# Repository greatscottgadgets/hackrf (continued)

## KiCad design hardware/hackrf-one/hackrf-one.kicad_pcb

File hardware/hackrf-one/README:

HackRF One is a wideband software radio transceiver with a USB interface.

hardware notes:

Schematic and layout files were designed in KiCad, an open source electronic
design automation package.

order of copper layers:
    Copper 1:  C1F (front)
    Copper 2:  C2
    Copper 3:  C3
    Copper 4:  C4B (back)

PCB description: 4 layer PCB 1.6 mm
    Copper    1   0.035 mm
    Prepreg 1-2   0.2104 mm
    Copper    2   0.0152 mm
    Core    2-3   1.065 mm
    Copper    3   0.0152 mm
    Prepreg 3-4   0.2104 mm
    Copper    4   0.035 mm

7628 prepreg with Er=4.6 (+/- 0.1)
required impedance: 50 ohm (+/- 5%) 11.55 mil microstrip impedance
double side solder mask green
single side silkscreen white
5 mil min trace width and
5 mil min isolation

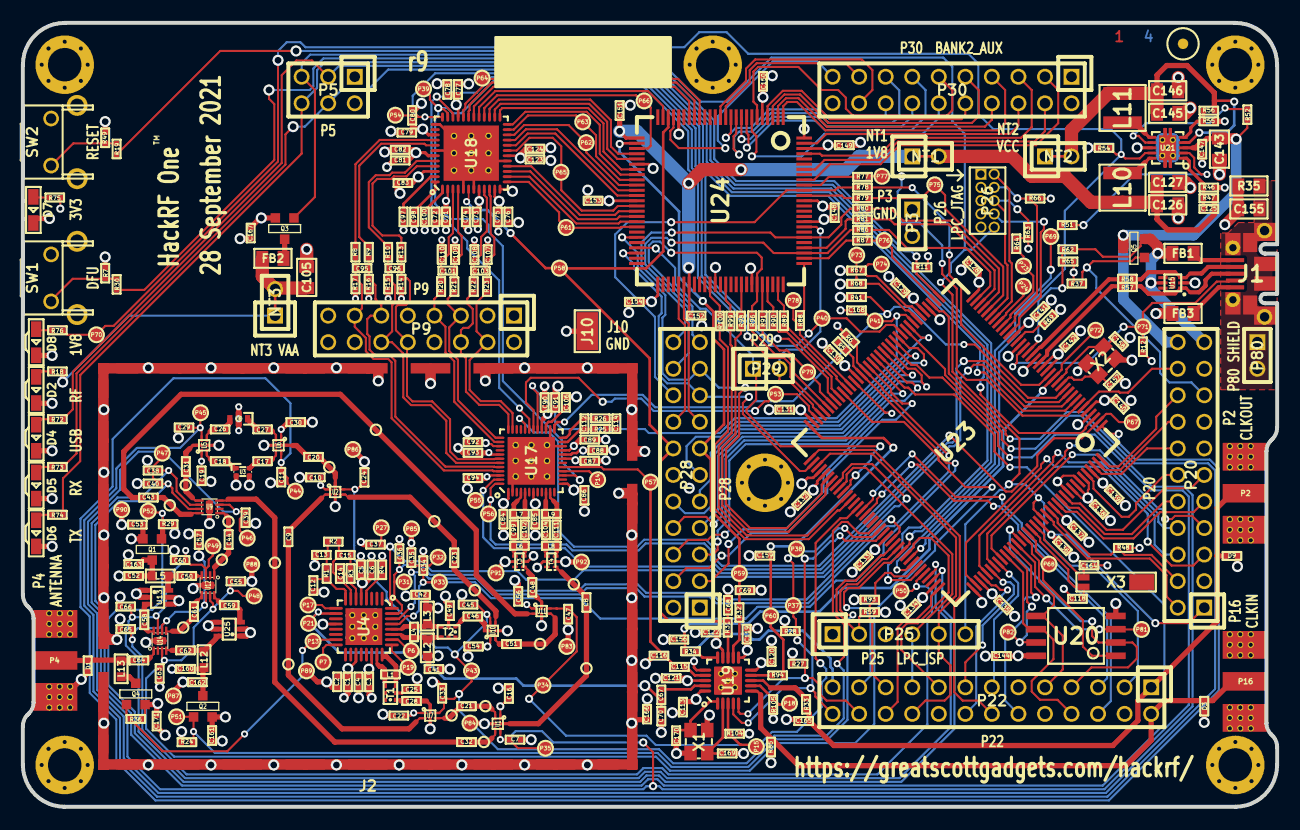
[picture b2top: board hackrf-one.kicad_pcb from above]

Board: 4 copper layers, 120.0 x 75.0 mm, 431 parts (0 on the bottom side), 315 nets.

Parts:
C1, C3, C5, C7, C11, C24, C29, C33, C34, C35, C36, C37, C38, C39, C40, C45, C47, C55, C57, C60, C63, C65, C66, C67, C115, C125: 33pF; GSG-0402
C2, C4, C6, C10, C16, C19, C22, C30, C54, C56, C87, C88, C89, C92, C93, C162, C163: 10nF; GSG-0402
C8, C21, C32, C43, C48, C51, C84, C85, C86, C94, C95, C96, C99, C101, C102, C103, C107, C108, C109, C110: 22pF; GSG-0402
C9, C17, C18, C20, C23, C25, C28, C31, C44, C46, C49, C50, C58, C59, C61, C62, C64, C71, C73, C75, C77, C79, C81, C83, C91, C113, C119, C120, C121, C122, C123, C128, C129, C130, C131, C132, C133, C134, C135, C136, C137, C138, C139, C140, C141, C142, C144, C147, C148, C149, C150, C151, C152, C153, C154, C166, C167: 100nF; GSG-0402
C12, C13: 330pF; GSG-0402
C14: 8p2; GSG-0402
C15, C112: 180pF; GSG-0402
C26, C27, C116, C156: 47pF; GSG-0402
C41, C42, C52, C68, C69, C70, C90, C159, C160, C165, C168: 100pF; GSG-0402
C53, C106, C161, C171: 1uF; GSG-0402
C72, C74, C76, C78, C80, C82, C124: 2.2uF; GSG-0402
C97, C98, C100: 330nF; GSG-0402
C104, C111: 3pF; GSG-0402
C105, C126, C127, C143, C145, C146: 10uF; GSG-0805
C114: 3.3nF; GSG-0402
C118, C157, C158, C164: 18pF; GSG-0402
C155: DNP; GSG-0805
C169, C170: 1.8pF; GSG-0402
D1, D3, D9: GSG-DIODE-TVS-BI; GSG-0402
D2: VAALED; LTST-S220
D4: USBLED; LTST-S220
D5: RXLED; LTST-S220
D6: TXLED; LTST-S220
D7: VCCLED; LTST-S220
D8: 1V8LED; LTST-S220
FB1, FB2, FB3: FILTER; GSG-0805
J1: USB-MICRO-B; GSG-USB-MICROB-FCI-10103592-EXT
J2: RF-SHIELD-FRAME; GSG-SHIELD-BMI-S-230
J3: RF-SHIELD-COVER; GSG-NULL-MODULE
J4, J5, J6, J7, J8, J9: MOUNTING_HOLE; GSG-HOLE126MIL-COPPER
J10: GND_CLIP; GSG-TEST-POINT-S1751-46R
L1, L4, L6, L8, L9: DNP; GSG-0402
L2, L3, L5, L12, L13: 10uH; GSG-0603
L7: 6.2nH; GSG-0402
L10, L11: 4u7; GSG-NRG4026
MARK1MM: VAL**; GSG-MARK1MM
NT1: 1V8; HEADER-1x2-SHORTED
NT2: VCC; HEADER-1x2-SHORTED
NT3: VAA; HEADER-1x2-SHORTED
P2: CLKOUT; GSG-SMA-73251-2120
P3: GND; GSG-HEADER-NOMARK-1x2
P4: ANTENNA; GSG-SMA-73251-2120
P5: LEDS; GSG-HEADER-2x3
P6: GPO4; GSG-TESTPOINT-50MIL
P7: GPO2; GSG-TESTPOINT-50MIL
P9: BASEBAND; GSG-HEADER-2x8
P13: GPO1; GSG-TESTPOINT-50MIL
P14: XCVR_CLKOUT; GSG-TESTPOINT-50MIL
P15: INTR; GSG-TESTPOINT-50MIL
P16: CLKIN; GSG-SMA-73251-2120
P17: GPO6; GSG-TESTPOINT-50MIL
P18: OEB; GSG-TESTPOINT-50MIL
P19: GPO3; GSG-TESTPOINT-50MIL
P20: GPIO; GSG-HEADER-2x11
P21: REF_IN; GSG-TESTPOINT-50MIL
P22: I2S; GSG-HEADER-2x13
P23: DBGEN; GSG-TESTPOINT-50MIL
P24: TRST; GSG-TESTPOINT-50MIL
P25: LPC_ISP; GSG-HEADER-1x6
P26: LPC_JTAG; GSG-50MIL-HEADER-2x5-TH
P27: MIXER_SDATA; GSG-TESTPOINT-50MIL
P28: SD; GSG-HEADER-2x11
P29: CPLD_JTAG; GSG-HEADER-1x2
P30: BANK2_AUX; GSG-HEADER-2x10
P31: MIXER_SCLK; GSG-TESTPOINT-50MIL
P32: MIXER_ENX; GSG-TESTPOINT-50MIL
P33: MIXER_RESETX; GSG-TESTPOINT-50MIL
P34: MIX_BYPASS; GSG-TESTPOINT-50MIL
P35: !MIX_BYPASS; GSG-TESTPOINT-50MIL
P37: SCL; GSG-TESTPOINT-50MIL
P38: SDA; GSG-TESTPOINT-50MIL
P39: SSP1_SCK; GSG-TESTPOINT-50MIL
P40: SSP1_COPI; GSG-TESTPOINT-50MIL
P41: SSP1_CIPO; GSG-TESTPOINT-50MIL
P43: RX; GSG-TESTPOINT-50MIL
P44: HP; GSG-TESTPOINT-50MIL
P45: LP; GSG-TESTPOINT-50MIL
P46: TX_MIX_BP; GSG-TESTPOINT-50MIL
P47: RX_MIX_BP; GSG-TESTPOINT-50MIL
P48: TX_AMP; GSG-TESTPOINT-50MIL
P49: RX_AMP; GSG-TESTPOINT-50MIL
P50: AMP_BYPASS; GSG-TESTPOINT-50MIL
P51: !TX_AMP_PWR; GSG-TESTPOINT-50MIL
P52: !RX_AMP_PWR; GSG-TESTPOINT-50MIL
P53: CS_XCVR; GSG-TESTPOINT-50MIL
P54: CS_AD; GSG-TESTPOINT-50MIL
P55: TXENABLE; GSG-TESTPOINT-50MIL
P56: RXENABLE; GSG-TESTPOINT-50MIL
P57: XTAL2; GSG-TESTPOINT-50MIL
P58: GCK1; GSG-TESTPOINT-50MIL
P59: GCK2; GSG-TESTPOINT-50MIL
P60: SGPIO_CLK; GSG-TESTPOINT-50MIL
P61: DA0; GSG-TESTPOINT-50MIL
P62: DA7; GSG-TESTPOINT-50MIL
P63: DD0; GSG-TESTPOINT-50MIL
P64: DD9; GSG-TESTPOINT-50MIL
P65: DA4; GSG-TESTPOINT-50MIL
P66: DD5; GSG-TESTPOINT-50MIL
P67: RSSI; GSG-TESTPOINT-50MIL
P68: SPIFI_CS; GSG-TESTPOINT-50MIL
P69: VREGMODE; GSG-TESTPOINT-50MIL
P70: EN_1V8; GSG-TESTPOINT-50MIL
P71: ID; GSG-TESTPOINT-50MIL
P72, P75, P76, P77, P78, P79: GP_CLKIN; GSG-TESTPOINT-50MIL
P73: P1_2; GSG-TESTPOINT-50MIL
P74: P1_1; GSG-TESTPOINT-50MIL
P80: SHIELD; GSG-HEADER-NOMARK-1x2
P81: SPIFI_SIO2; GSG-TESTPOINT-50MIL
P82: SPIFI_SIO3; GSG-TESTPOINT-50MIL
P83, P84, P85, P86, P87, P88, P89, P90, P91, P92: GND; GSG-TESTPOINT-50MIL
Q1, Q2, Q3, Q4, Q5: MOSFET_P; SOT23-3
R1, R2, R72, R75: 470; GSG-0402
R3: 22k; GSG-0402
R4: 51k; GSG-0402
R5, R6, R7, R11, R12, R24, R29, R36, R37, R41, R48, R49, R51, R52, R54, R59, R62, R63, R64, R66, R67, R68, R85, R93, R104, R105: 10k; GSG-0402
R8, R9, R10, R13, R73, R76: 1k; GSG-0402
R14, R15, R16, R17: 4k7; GSG-0402
R18, R27, R28, R74: 1k8; GSG-0402
R19, R30, R31, R32, R33, R34, R77, R78, R79, R80, R81, R86, R87, R88, R89, R90, R91, R94, R96, R98, R99, R100: 39; GSG-0402
R20, R21, R22, R23, R57, R58: 0; GSG-0402
R25, R26: 475; GSG-0402
R35: DNP; GSG-0805
R46, R55: 162k; GSG-0402
R47: 330k; GSG-0402
R56: 715k; GSG-0402
R65: 18k; GSG-0402
R69: 12k; GSG-0402
SW1: DFU; GSG-SWITCH-FSMRA
SW2: RESET; GSG-SWITCH-FSMRA
T1: MIX_IN_BALUN; GSG-B0310J50100AHF
T2: MIX_OUT_BALUN; GSG-B0310J50100AHF
T3: RX_BALUN; GSG-2500BL14M100
T4: TX_BALUN; GSG-2500BL14M100
TESTPOINT-30MIL-MASKONLY, TESTPOINT-30MIL-MASKONLY#2, TESTPOINT-30MIL-MASKONLY#3, TESTPOINT-30MIL-MASKONLY#4, TESTPOINT-30MIL-MASKONLY#5, TESTPOINT-30MIL-MASKONLY#6, TESTPOINT-30MIL-MASKONLY#7, TESTPOINT-30MIL-MASKONLY#8, TESTPOINT-30MIL-MASKONLY#9, TESTPOINT-30MIL-MASKONLY#10, TESTPOINT-30MIL-MASKONLY#11, TESTPOINT-30MIL-MASKONLY#12, TESTPOINT-30MIL-MASKONLY#13, TESTPOINT-30MIL-MASKONLY#14, TESTPOINT-30MIL-MASKONLY#15, TESTPOINT-30MIL-MASKONLY#16, TESTPOINT-30MIL-MASKONLY#17: VAL**; GSG-TESTPOINT-30MIL-MASKONLY
U1, U2, U5, U6, U7, U10, U11: SKY13453; SKY13350-385LF
U3: RX_LOWPASS_FILTER; GSG-LP0603
U4: RFFC5072; GSG-QFN32
U8: RX_HIGHPASS_FILTER; GSG-HP-DEA
U9, U12, U14: SKY13317; GSG-SKY13317-373LF
U13, U25: MGA-81563; GSG-SOT363
U15: TVS; GSG-LXES1TBCC2-004
U17: MAX2837; GSG-QFN48-6
U18: MAX5864; GSG-QFN48-7
U19: SI5351C; GSG-QFN20-4
U20: W25Q80; GSG-SOIC8-208
U21: TPS62410; GSG-S-PVSON-N10
U23: LPC4320FBD144; GSG-LQFP144
U24: GSG-XC2C64A-7VQG100C; GSG-VQ100
X1: GSG-XTAL4PIN; GSG-XTAL3.2x2.5mm
X2: MCU_XTAL; GSG-XTAL3.2x2.5mm
X3: RTC_XTAL; GSG-XTAL-AB26TRQ

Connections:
!MIX_BYPASS: C7.2, C38.2, P35.1, U1.5, U9.6, U23.50
!RX_AMP_PWR: P52.1, Q1.1, R29.2, U23.106
!TX_AMP_PWR: P51.1, Q2.1, R24.1, U23.97
!VAA_ENABLE: P5.5, Q3.1, R11.2, U23.37
+1V8: C151.1, C152.1, NT1.1, U24.26, U24.57
/baseband/CLK0: R31.2, U19.13
/baseband/CLK1: R32.2, U19.12
/baseband/CLK2: R94.2, U19.9
/baseband/CLK3: R33.2, U19.8
/baseband/CLK5: C115.1, U19.17
/baseband/COM: C97.1, U18.47
/baseband/CPOUT+: C112.2, R25.1, U17.23
/baseband/CPOUT-: C112.1, R26.1, U17.24
/baseband/IA+: C101.1, C110.1, R20.1, U18.3
/baseband/IA-: C101.2, C109.1, R21.1, U18.4
/baseband/ID+: R13.1, U18.45
/baseband/ID-: R10.1, U18.44
/baseband/INTR: P15.1, R104.2, U19.3
/baseband/OEB: P18.1, R105.2, U19.7
/baseband/QA+: C103.2, C107.1, R23.1, U18.10
/baseband/QA-: C103.1, C108.1, R22.1, U18.9
/baseband/QD+: R8.1, U18.40
/baseband/QD-: R9.1, U18.41
/baseband/REFN: C98.1, U18.48
/baseband/REFP: C100.1, U18.1
/baseband/RXBBI+: P9.7, R20.2, U17.38
/baseband/RXBBI-: P9.5, R21.2, U17.37
/baseband/RXBBQ+: P9.6, R22.2, U17.36
/baseband/RXBBQ-: P9.4, R23.2, U17.35
/baseband/TXBBI+: C96.1, P9.12, R10.2, R15.1, U17.43
/baseband/TXBBI-: C96.2, P9.10, R13.2, R14.1, U17.42
/baseband/TXBBQ+: C95.2, P9.11, R9.2, R16.1, U17.44
/baseband/TXBBQ-: C95.1, P9.13, R8.2, R17.1, U17.45
/baseband/XA: C170.2, U19.1, X1.3
/baseband/XB: C169.2, U19.2, X1.1
/baseband/XCVR_CLKOUT: P14.1, U17.16
/baseband/XTAL2: C115.2, C116.1, P57.1, U17.17
/frontend/!ANT_BIAS: P13.1, Q4.1, R36.1, U4.15
/frontend/REF_IN: C67.2, C70.1, P21.1, U4.10
/frontend/RX_AMP_IN: C58.1, U14.8
/frontend/RX_AMP_OUT: C50.2, U12.4
/frontend/TX_AMP_IN: C59.1, U12.8
/frontend/TX_AMP_OUT: C62.1, U14.4
/mcu/usb/power/ADC0_0: P20.20, U23.6
/mcu/usb/power/ADC0_2: P20.16, U23.143
/mcu/usb/power/ADC0_5: P20.18, U23.144
/mcu/usb/power/ADC0_6: P20.14, U23.142
/mcu/usb/power/B1AUX13: P28.16, U24.55
/mcu/usb/power/B1AUX14: P28.15, U24.56
/mcu/usb/power/B2AUX1: P30.18, U24.13
/mcu/usb/power/B2AUX2: P30.17, U24.12
/mcu/usb/power/B2AUX3: P30.16, U24.11
/mcu/usb/power/B2AUX4: P30.15, U24.10
/mcu/usb/power/B2AUX5: P30.14, U24.9
/mcu/usb/power/B2AUX6: P30.13, U24.8
/mcu/usb/power/B2AUX7: P30.12, U24.7
/mcu/usb/power/B2AUX8: P30.11, U24.6
/mcu/usb/power/B2AUX9: P30.10, U24.4
/mcu/usb/power/B2AUX10: P30.9, U24.3
/mcu/usb/power/B2AUX11: P30.8, U24.2
/mcu/usb/power/B2AUX12: P30.7, U24.1
/mcu/usb/power/B2AUX13: P30.6, U24.99
/mcu/usb/power/B2AUX14: P30.5, U24.97
/mcu/usb/power/B2AUX15: P30.4, U24.94
/mcu/usb/power/B2AUX16: P30.3, U24.92
/mcu/usb/power/BANK2F3M1: R77.2, U24.91
/mcu/usb/power/BANK2F3M2: P28.18, R78.2, U24.90
/mcu/usb/power/BANK2F3M3: R79.2, U24.89
/mcu/usb/power/BANK2F3M4: P28.22, R80.2, U24.81
/mcu/usb/power/BANK2F3M5: R81.2, U24.79
/mcu/usb/power/BANK2F3M6: P28.20, R86.2, U24.78
/mcu/usb/power/BANK2F3M7: R87.2, U24.77
/mcu/usb/power/BANK2F3M8: R88.2, U24.76
/mcu/usb/power/BANK2F3M9: R89.2, U24.74
/mcu/usb/power/BANK2F3M10: R90.2, U24.72
/mcu/usb/power/BANK2F3M11: R91.2, U24.71
/mcu/usb/power/BANK2F3M12: P28.21, R96.2, U24.70
/mcu/usb/power/BANK2F3M14: R98.2, U24.67
/mcu/usb/power/BANK2F3M15: R99.2, U24.64
/mcu/usb/power/BANK2F3M16: R100.2, U24.61
/mcu/usb/power/CPLD_TCK: P28.17, U23.74, U24.48
/mcu/usb/power/CPLD_TDI: P28.19, U23.78, U24.45
/mcu/usb/power/CPLD_TDO: P29.2, U23.69, U24.83
/mcu/usb/power/CPLD_TMS: P29.1, U23.82, U24.47
/mcu/usb/power/DBGEN: P23.1, R64.1, U23.28
/mcu/usb/power/DM: R58.1, U23.20
/mcu/usb/power/DP: R57.1, U23.18
/mcu/usb/power/EN1V8: P70.1, R54.2, R76.2, U21.9, U23.100
/mcu/usb/power/GCK0: P30.19, U24.22
/mcu/usb/power/GPIO3_8: P20.5, U23.110
/mcu/usb/power/GPIO3_9: P20.6, U23.113
/mcu/usb/power/GPIO3_10: P20.7, U23.115
/mcu/usb/power/GPIO3_11: P20.8, U23.117
/mcu/usb/power/GPIO3_12: P20.9, U23.132
/mcu/usb/power/GPIO3_13: P20.10, U23.133
/mcu/usb/power/GPIO3_14: P20.11, U23.134
/mcu/usb/power/GPIO3_15: P20.12, U23.140
/mcu/usb/power/GP_CLKIN: C156.1, P72.1, R34.1, U23.14
/mcu/usb/power/I2C1_SCL: P22.5, U23.88
/mcu/usb/power/I2C1_SDA: P22.6, U23.87
/mcu/usb/power/I2S0_RX_MCLK: P22.14, U23.73
/mcu/usb/power/I2S0_RX_SCK: P22.12, U23.120
/mcu/usb/power/I2S0_RX_SDA: P22.13, U23.116
/mcu/usb/power/I2S0_RX_WS: P22.15, U23.114
/mcu/usb/power/I2S0_TX_MCLK: P22.17, U23.99
/mcu/usb/power/I2S0_TX_SCK: P22.16, U23.112
/mcu/usb/power/ISP: P25.2, R59.2, U23.96
/mcu/usb/power/LED1: P5.3, R72.2, U23.3
/mcu/usb/power/LED2: P5.4, R73.2, U23.8
/mcu/usb/power/LED3: P5.6, R74.2, U23.103
/mcu/usb/power/P1_1: P74.1, R67.1, U23.42
/mcu/usb/power/P1_2: P73.1, R68.1, U23.43
/mcu/usb/power/P2_8: P22.23, R30.1, U23.98
/mcu/usb/power/P2_9: P22.21, R93.1, U23.102
/mcu/usb/power/P2_13: P22.22, U23.108
/mcu/usb/power/REG_OUT1: C145.2, C146.2, L11.1, NT2.2, R56.1, U21.4
/mcu/usb/power/REG_OUT2: C125.1, C126.1, C127.1, L10.2, NT1.2, R47.1
/mcu/usb/power/RESET: P22.3, P25.6, P26.10, R19.1, U23.128
/mcu/usb/power/RREF: R69.1, U23.24
/mcu/usb/power/RTCX1: C118.1, U23.125, X3.2
/mcu/usb/power/RTCX2: C164.1, U23.126, X3.1
/mcu/usb/power/RTC_ALARM: P20.2, U23.129
/mcu/usb/power/SD_CD: P28.3, U23.60
/mcu/usb/power/SD_CLK: P28.11, U23.45
/mcu/usb/power/SD_CMD: P28.9, U23.49
/mcu/usb/power/SD_DAT0: P28.7, U23.52
/mcu/usb/power/SD_DAT1: P28.6, U23.53
/mcu/usb/power/SD_DAT2: P28.5, U23.55
/mcu/usb/power/SD_DAT3: P28.4, U23.56
/mcu/usb/power/SD_POW: P28.10, U23.48
/mcu/usb/power/SD_VOLT0: P28.8, U23.51
/mcu/usb/power/SGPIO0: P75.1, R79.1, U23.32
/mcu/usb/power/SGPIO1: R81.1, U23.34
/mcu/usb/power/SGPIO2: R89.1, U23.62
/mcu/usb/power/SGPIO3: R90.1, U23.64
/mcu/usb/power/SGPIO4: R98.1, U23.79
/mcu/usb/power/SGPIO5: R99.1, U23.83
/mcu/usb/power/SGPIO6: R100.1, U23.84
/mcu/usb/power/SGPIO7: P76.1, R87.1, U23.38
/mcu/usb/power/SGPIO9: P77.1, R77.1, U23.7
/mcu/usb/power/SGPIO10: P78.1, R88.1, U23.61
/mcu/usb/power/SGPIO11: P79.1, R91.1, U23.66
/mcu/usb/power/SGPIO12: R96.1, U23.67
/mcu/usb/power/SGPIO13: R78.1, U23.15
/mcu/usb/power/SGPIO14: R80.1, U23.33
/mcu/usb/power/SGPIO15: R86.1, U23.35
/mcu/usb/power/SPIFI_CIPO: P22.7, U20.2, U23.122
/mcu/usb/power/SPIFI_COPI: P22.9, U20.5, U23.123
/mcu/usb/power/SPIFI_CS: P68.1, U20.1, U23.124
/mcu/usb/power/SPIFI_SCK: P22.8, U20.6, U23.118
/mcu/usb/power/SPIFI_SIO2: P81.1, U20.3, U23.121
/mcu/usb/power/SPIFI_SIO3: P82.1, U20.7, U23.119
/mcu/usb/power/TCK: P26.4, R66.2, U23.27
/mcu/usb/power/TDI: P26.8, U23.26
/mcu/usb/power/TDO: P26.6, R63.1, U23.31
/mcu/usb/power/TMS: P26.2, U23.30
/mcu/usb/power/U0_RXD: P22.19, P25.4, U23.81
/mcu/usb/power/U0_TXD: P22.20, P25.5, U23.75
/mcu/usb/power/USB_SHIELD: C155.1, J1.0, P80.1, P80.2, R35.1
/mcu/usb/power/VBAT: C136.1, P20.1, U23.127
/mcu/usb/power/VBUS: FB1.2, P20.21, Q5.2, R62.2, U15.5
/mcu/usb/power/VBUSCTRL: P20.17, Q5.1, R37.2
/mcu/usb/power/VIN: C143.1, C147.1, P20.22, Q5.3, R52.1, U21.3
/mcu/usb/power/VREGMODE: P69.1, R51.2, U23.101
/mcu/usb/power/WAKEUP: P20.4, R48.2, U23.130
/mcu/usb/power/XTAL1: C157.1, U23.12, X2.1
/mcu/usb/power/XTAL2: C158.1, U23.13, X2.3
AMP_BYPASS: C57.1, C65.2, P50.1, U12.6, U14.6, U23.104
CLK6: P22.25, U19.16
CLKIN: D3.2, P16.1, P22.2, R85.1, U19.6
CLKOUT: C165.1, D9.2, P2.1, P22.1, R33.1
CS_AD: P54.1, U18.36, U23.65
CS_XCVR: P53.1, U17.30, U23.70
DA0: P61.1, U18.13, U24.43
DA1: U18.14, U24.42
DA2: U18.15, U24.41
DA3: U18.16, U24.40
DA4: P65.1, U18.19, U24.39
DA5: U18.20, U24.37
DA6: U18.21, U24.36
DA7: P62.1, U18.22, U24.35
DD0: P63.1, U18.23, U24.34
DD1: U18.24, U24.33
DD2: U18.25, U24.32
DD3: U18.26, U24.30
DD4: U18.27, U24.29
DD5: P66.1, U18.28, U24.28
DD6: U18.29, U24.24
DD7: U18.30, U24.19
DD8: U18.31, U24.18
DD9: P64.1, U18.32, U24.17
GCK1: C68.1, P28.14, P58.1, R31.1, U18.6, U24.23
GCK2: C69.1, P28.13, P59.1, R32.1, U24.27
GND: C1.2, C2.2, C3.2, C4.2, C5.2, C6.2, C7.1, C10.1, C11.1, C12.2, C13.2, C16.2, C19.1, C22.1, C24.1, C25.2, C29.2, C30.2, C33.2, C34.2, C35.2, C36.2, C37.2, C38.1, C39.1, C40.1, C41.2, C42.2, C45.1, C47.1, C49.1, C52.2, C53.2, C54.2, C55.2, C56.2, C57.2, C60.1, C63.2, C65.1, C66.1, C68.2, C69.2, C70.2, C71.2, C72.2, C73.2, C74.2, C75.2, C76.2, C77.2, C78.2, C79.2, C80.2, C81.2, C82.2, C83.2, C84.2, C85.2, C86.2, C87.2, C88.2, C89.2, C90.2, C91.2, C92.2, C93.2, C94.2, C97.2, C98.2, C100.2, C105.2, C106.2, C107.2, C108.2, C109.2, C110.2, C113.2, C116.2, C118.2, C119.2, C120.2, C121.2, C122.2, C123.2, C124.2, C126.2, C127.2, C128.2, C129.2, C130.2, C131.2, C132.2, C133.2, C134.2, C135.2, C136.2, C137.2, C138.2, C139.2, C140.2, C141.2, C142.2, C143.2, C144.2, C145.1, C146.1, C147.2, C148.2, C149.2, C150.2, C151.2, C152.2, C153.2, C154.2, C155.2, C156.2, C157.2, C158.2, C159.2, C160.2, C161.2, C162.1, C163.1, C164.2, C165.2, C166.2, C167.2, C168.2, C169.1, C170.1, C171.2, D1.1, D2.1, D3.1, D4.1, D5.1, D6.1, D7.1, D8.1, D9.1, FB3.2, J2.0, J4.1, J5.1, J6.1, J7.1, J8.1, J9.1, J10.1, P2.2, P3.1, P3.2, P4.2, P5.1, P9.1, P9.2, P9.3, P9.8, P9.9, P9.14, P9.15, P9.16, P16.2, P20.13, P20.15, P20.19, P22.4, P22.10, P22.18, P25.1, P26.3, P26.5, P26.9, P28.2, P28.12, P30.2, P30.20, P83.1, P84.1, P85.1, P86.1, P87.1, P88.1, P89.1, P90.1, P91.1, P92.1, R4.1, R7.2, R14.2, R15.2, R16.2, R17.2, R35.2, R37.1, R41.1, R46.1, R54.1, R55.1, R65.1, R68.2, R69.2, R85.2, R93.2, SW1.0, SW2.0, SW2.1, T3.2, T3.5, T4.2, T4.5, U1.3, U2.3, U3.2, U3.3, U4.0, U4.12, U5.3, U6.3, U7.3, U8.2, U8.4, U9.0, U10.3, U11.3, U12.0, U13.1, U13.2, U13.4, U13.5, U14.0, U15.2, U17.0, U17.2, U17.22, U17.26, U18.0, U18.5, U18.7, U18.12, U18.17, U18.37, U18.42, U19.0, U20.4, U21.0, U21.8, U23.4, U23.19, U23.23, U23.40, U23.76, U23.109, U23.135, U23.138, U24.21, U24.31, U24.62, U24.69, U24.84, U24.100, U25.1, U25.2, U25.4, U25.5, X1.2, X1.4, X2.2, X2.4
HP: C11.2, P44.1, U6.5, U23.1
LP: C29.1, P45.1, U5.5, U23.39
MCU_CLK: R34.2, U19.15
MIXER_ENX: C35.1, P32.1, R6.2, U4.30, U23.57
MIXER_RESETX: C34.1, P33.1, R5.2, U4.29, U23.58
MIXER_SCLK: C36.1, P31.1, U4.31, U23.95
MIXER_SDATA: C37.1, P27.1, U4.32, U23.80
MIX_BYPASS: C47.2, P34.1, U11.5, U23.86
MIX_CLK: C67.1, U19.19
unnamed: C8.2, U1.6
unnamed: C9.1, U7.2
unnamed: C9.2, U2.2
unnamed: C12.1, R1.2, U4.8
unnamed: C13.1, R1.1, R2.2
unnamed: C14.1, C15.1, R2.1, U4.7
unnamed: C14.2, R3.1, U4.6
unnamed: C15.2, R3.2
unnamed: C17.1, U3.4
unnamed: C17.2, U6.4
unnamed: C18.1, U5.2
unnamed: C18.2, U3.1
unnamed: C20.1, U6.6
unnamed: C20.2, U2.6
unnamed: C21.1, U1.2
unnamed: C21.2, U7.4
unnamed: C23.1, U10.4
unnamed: C23.2, U2.4
unnamed: C25.1, T1.2
unnamed: C26.1, U8.3
unnamed: C26.2, U5.4
unnamed: C27.1, U8.1
unnamed: C27.2, U6.2
unnamed: C28.1, T1.1
unnamed: C28.2, U7.6
unnamed: C31.1, U9.5
unnamed: C31.2, U5.6
unnamed: C32.1, U1.4
unnamed: C32.2, U9.4
unnamed: C43.1, U9.8
unnamed: C43.2, U11.2
unnamed: C44.1, U12.1
unnamed: C44.2, U9.1
unnamed: C46.1, U10.6
unnamed: C46.2, T2.1
unnamed: C48.1, U11.6
unnamed: C49.2, T2.2
unnamed: C50.1, L5.2, U13.6
unnamed: C51.1, U11.4
unnamed: C51.2, U10.2
unnamed: C58.2, U13.3
unnamed: C59.2, U25.3
unnamed: C61.1, U14.5
unnamed: C61.2, U12.5
unnamed: C62.2, L12.2, U25.6
unnamed: C64.1, U14.1
unnamed: C64.2, D1.2, L13.2, P4.1
unnamed: C99.1, L7.1, U17.4
unnamed: C99.2, L6.1, T3.4
unnamed: C102.1, L7.2, U17.5
unnamed: C102.2, L6.2, T3.3
unnamed: C104.1, L9.1, U17.10
unnamed: C104.2, L8.1, T4.4
unnamed: C105.1, FB2.2, NT3.2
unnamed: C106.1, U17.27
unnamed: C111.1, L9.2, U17.11
unnamed: C111.2, L8.2, T4.3
unnamed: C114.1, R26.2
unnamed: C114.2, R25.2
unnamed: C125.2, R46.2, R47.2, U21.1
unnamed: C160.1, C162.2, L12.1, Q2.3
unnamed: C52.1, C163.2, L5.1, Q1.3
unnamed: D2.2, R18.1
unnamed: D4.2, R72.1
unnamed: D5.2, R73.1
unnamed: D6.2, R74.1
unnamed: D7.2, R75.1
unnamed: D8.2, R76.1
unnamed: FB1.1, J1.1
unnamed: FB2.1, Q3.3
unnamed: FB3.1, J1.5
unnamed: J1.2, R58.2, U15.3
unnamed: J1.3, R57.2, U15.1
unnamed: J1.4, P71.1, R12.2, U23.22
unnamed: L1.1, T1.4, U4.23
unnamed: L1.2, T1.3, U4.24
unnamed: L2.1, L4.2, T2.4, U4.27
unnamed: L3.1, L4.1, T2.3, U4.28
unnamed: L10.1, U21.10
unnamed: L11.2, U21.6
unnamed: L13.1, Q4.3
unnamed: P6.1, U4.26
unnamed: P7.1, U4.16
unnamed: P17.1, U4.9
unnamed: P19.1, U4.25
unnamed: P24.1, U23.29
unnamed: R4.2, U4.4
unnamed: R19.2, R49.2, SW2.2
unnamed: R7.1, R30.2, SW1.2
unnamed: R51.1, U21.2
unnamed: R52.2, U21.7
unnamed: R55.2, R56.2, U21.5
unnamed: R62.1, R65.2, U23.21
RSSI: P67.1, U17.32, U23.2
RX: C24.2, C33.1, C45.2, P43.1, U2.5, U7.5, U10.5, U23.91
RXENABLE: P56.1, U17.48, U23.10
RX_AMP: C60.2, C66.2, P49.1, U12.3, U14.7, U23.105
RX_IF: C48.2, T3.1
RX_MIX_BP: C40.2, P47.1, U9.7, U23.54
SCL: P22.26, P37.1, R28.2, U19.4, U23.92
SDA: P22.24, P38.1, R27.2, U19.5, U23.93
SGPIO_CLK: C159.1, P60.1, R94.1, U23.72
SSP1_CIPO: C168.1, P41.1, U17.29, U23.44
SSP1_COPI: P40.1, U17.31, U18.34, U23.47
SSP1_SCK: P39.1, U17.15, U18.35, U23.68
TXENABLE: P55.1, U17.47, U23.9
TX_AMP: C55.1, C63.1, P48.1, U12.7, U14.3, U23.63
TX_IF: C8.1, T4.1
TX_MIX_BP: C39.2, P46.1, U9.3, U23.46
VAA: C3.1, C4.1, C5.1, C6.1, C10.2, C16.1, C19.2, C22.2, C30.1, C41.1, C42.1, C53.1, C54.1, C56.1, C71.1, C72.1, C73.1, C74.1, C75.1, C76.1, C77.1, C78.1, C79.1, C80.1, C81.1, C82.1, C83.1, C84.1, C85.1, C86.1, C87.1, C89.1, C90.1, C91.1, C92.1, C93.1, C94.1, C161.1, C166.1, C171.1, L2.2, L3.2, NT3.1, Q1.2, Q2.2, Q4.2, R18.2, R24.2, R29.1, R36.2, U1.1, U2.1, U4.5, U4.22, U5.1, U6.1, U7.1, U10.1, U11.1, U17.1, U17.7, U17.13, U17.19, U17.21, U17.28, U17.39, U17.41, U17.46, U18.2, U18.8, U18.11, U18.33, U18.39, U18.43, U18.46
VCC: C1.1, C2.1, C88.1, C113.1, C119.1, C120.1, C121.1, C122.1, C123.1, C124.1, C128.1, C129.1, C130.1, C131.1, C132.1, C133.1, C134.1, C135.1, C137.1, C138.1, C139.1, C140.1, C141.1, C142.1, C144.1, C148.1, C149.1, C150.1, C153.1, C154.1, C167.1, NT2.1, P5.2, P20.3, P22.11, P26.1, P28.1, P30.1, Q3.2, R5.1, R6.1, R11.1, R12.1, R27.1, R28.1, R48.1, R49.1, R59.1, R63.2, R64.2, R66.1, R67.2, R75.2, R104.1, R105.1, SW1.1, U4.19, U17.20, U18.18, U19.10, U19.11, U19.14, U19.18, U19.20, U20.8, U23.5, U23.16, U23.17, U23.25, U23.36, U23.41, U23.59, U23.71, U23.77, U23.94, U23.107, U23.111, U23.131, U23.136, U23.137, U23.139, U23.141, U24.5, U24.38, U24.51, U24.88, U24.98
XCVR_EN: R41.2, U17.25, U23.11

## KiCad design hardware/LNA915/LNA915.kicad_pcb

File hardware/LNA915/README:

Copyright (c) 2014-2020 Great Scott Gadgets <info@greatscottgadgets.com>

These files are part of HackRF.

This is a free hardware design; you can redistribute it and/or modify
it under the terms of the GNU General Public License as published by
the Free Software Foundation; either version 2, or (at your option)
any later version.

This design is distributed in the hope that it will be useful,
but WITHOUT ANY WARRANTY; without even the implied warranty of
MERCHANTABILITY or FITNESS FOR A PARTICULAR PURPOSE.  See the
GNU General Public License for more details.

You should have received a copy of the GNU General Public License
along with this design; see the file COPYING.  If not, write to
the Free Software Foundation, Inc., 51 Franklin Street,
Boston, MA 02110-1301, USA.

LNA915 is a SAW filter and LNA for the 902 to 928 MHz ISM band.  It is designed
for in-line connection between an antenna and HackRF One and is powered by the
HackRF One.

hardware notes:

Schematic and layout files were designed in KiCad, an open source electronic
design automation package.

The PCB is designed to fit the Crystek SMA-KIT-1.5MF housing.

order of copper layers:
    Copper 1:  F (front)
    Copper 2:  In1
    Copper 3:  In2
    Copper 4:  B (back)

PCB description: 4 layer PCB 0.8 mm
    Copper       1:  0.035 mm (1 oz)
    Dielectric 1-2:  0.2 mm prepreg
    Copper       2:  0.0175 mm (0.5 oz)
    Dielectric 2-3:  0.265 mm core
    Copper       3:  0.0175 mm (0.5 oz)
    Dielectric 3-4:  0.2 mm prepreg
    Copper       4:  0.035 mm (1 oz)

7628 prepreg with Er=4.6
double side solder mask green
double side silkscreen white
7 mil minimum trace width
5 mil minimum isolation

PCBs of this specification are available from JLCPCB (JLC7628 4-layer 0.8 mm stackup).

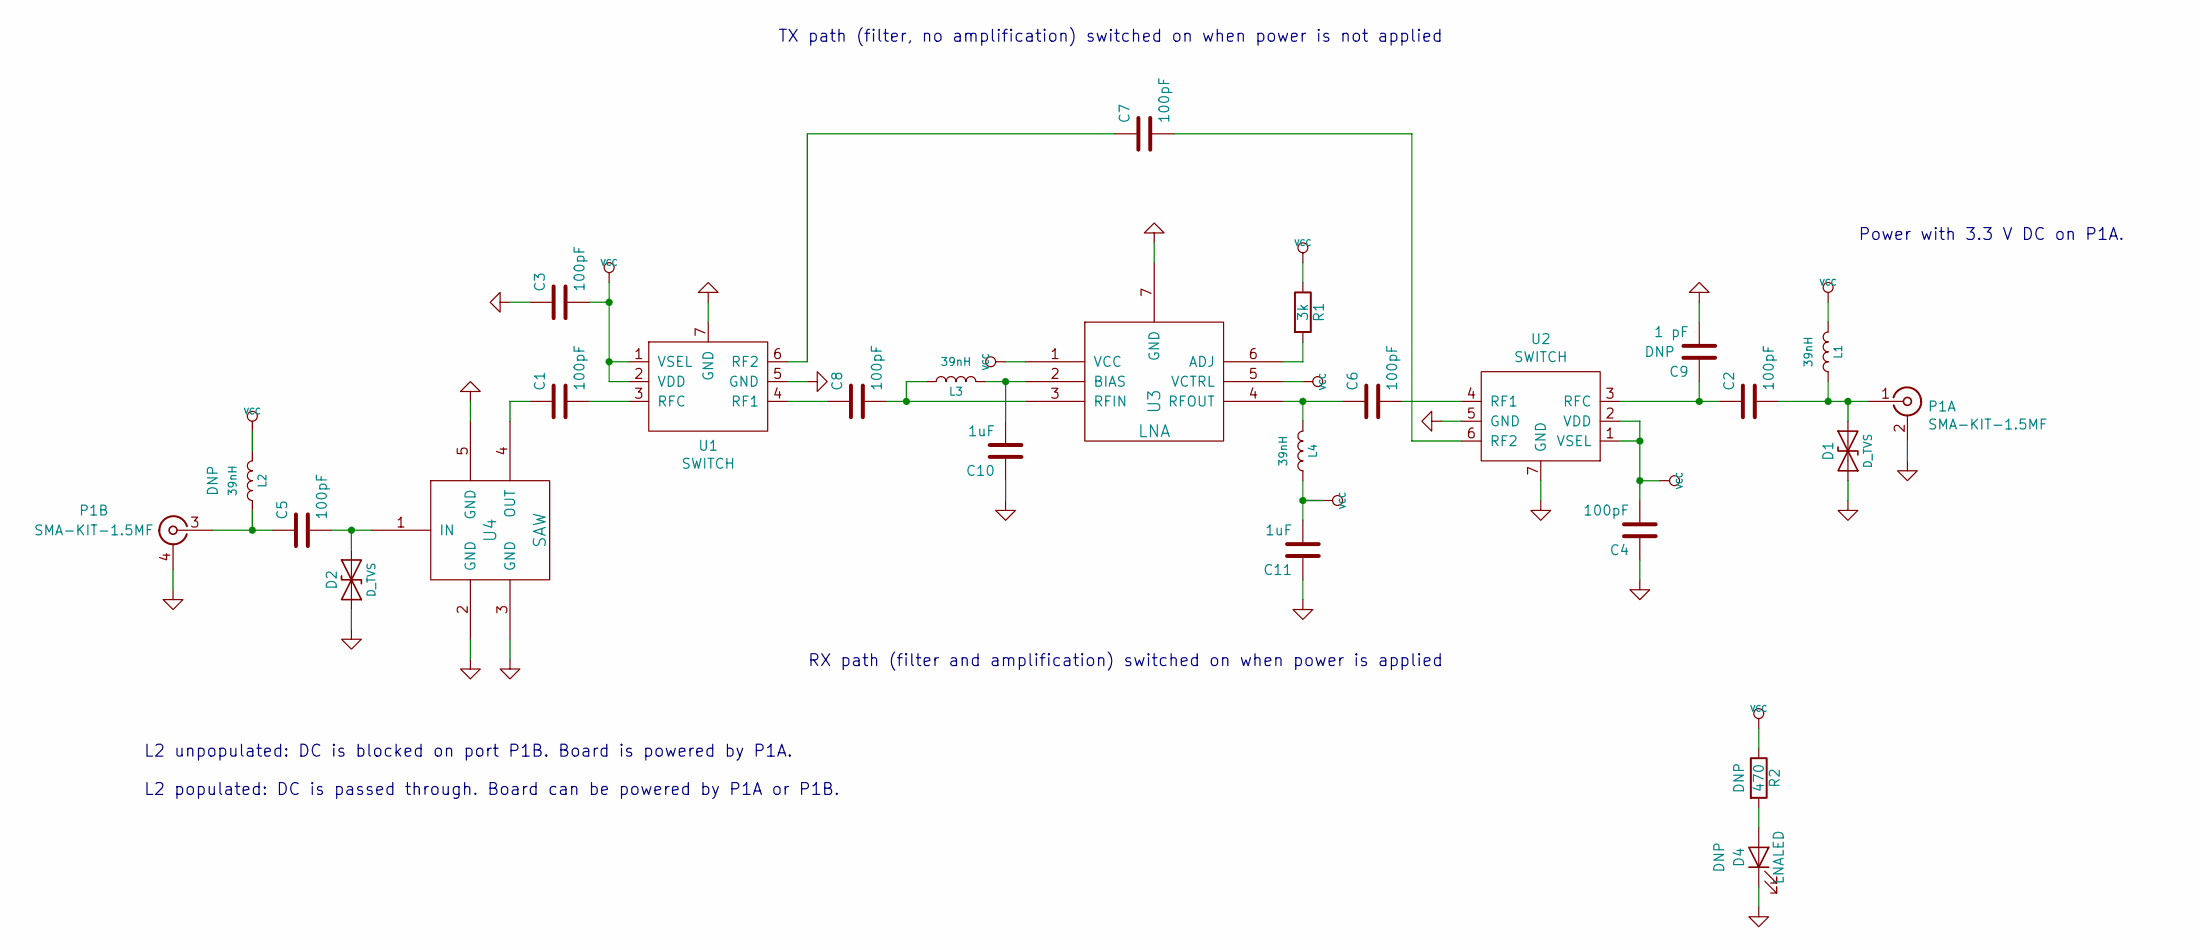
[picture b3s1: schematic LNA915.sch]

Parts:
C1, C2, C3, C4, C5, C6, C7, C8: 100pF; 0402; Part Number GCM1555C1H101JA16
C9: 1 pF; 0402
C10, C11: 1uF; 0402; Part Number LMK105BJ105KV-F
D1, D2: D_TVS; 0402; Part Number LXES15AAA1-153
D4: LNALED; 0402
L1, L2, L3, L4: 39nH; 0402; Part Number HK100539NJ-T
P1: SMA-KIT-1.5MF; Part Number SMA-KIT-1.5MF
R1: 3k; 0402; Part Number RMCF0402FT3K00
R2: 470; 0402; Part Number RMCF0402JT470R
U1, U2: SWITCH; GRF6011; Part Number GRF6011
U3: LNA; TSLP-7-1; Part Number BGB 741L7ESD E6327
U4: SAW; F5Q; Part Number FAR-F5QA-915M00-M2AK-J

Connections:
GND: C3.1, C4.1, C9.2, C10.1, C11.1, D1.1 (A1), D2.1 (A1), D4.1 (K), P1.2 (SHIELD), P1.4 (SHIELD), U1.5 (GND), U1.7 (GND), U2.5 (GND), U2.7 (GND), U3.7 (GND), U4.2 (GND), U4.3 (GND), U4.5 (GND)
unnamed: C1.1, U4.4 (OUT)
unnamed: C1.2, U1.3 (RFC)
unnamed: C2.1, C9.1, U2.3 (RFC)
unnamed: C2.2, D1.2 (A2), L1.1, P1.1 (RF)
unnamed: C5.1, L2.1, P1.3 (RF)
unnamed: C5.2, D2.2 (A2), U4.1 (IN)
unnamed: C6.1, L4.2, U3.4 (RFOUT)
unnamed: C6.2, U2.4 (RF1)
unnamed: C7.1, U1.6 (RF2)
unnamed: C7.2, U2.6 (RF2)
unnamed: C8.1, U1.4 (RF1)
unnamed: C8.2, L3.1, U3.3 (RFIN)
unnamed: C10.2, L3.2, U3.2 (BIAS)
unnamed: D4.2 (A), R2.2
unnamed: R1.2, U3.6 (ADJ)
VCC: C3.2, C4.2, C11.2, L1.2, L2.2, L4.1, R1.1, R2.1, U1.1 (VSEL), U1.2 (VDD), U2.1 (VSEL), U2.2 (VDD), U3.1 (VCC), U3.5 (VCTRL)

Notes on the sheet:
Power with 3.3 V DC on P1A.
TX path (filter, no amplification) switched on when power is not applied
RX path (filter and amplification) switched on when power is applied
L2 unpopulated: DC is blocked on port P1B. Board is powered by P1A. L2 populated: DC is passed through. Board can be powered by P1A or P1B.

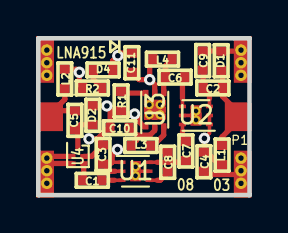
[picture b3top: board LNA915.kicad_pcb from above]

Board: 4 copper layers, 11.7 x 8.7 mm, 25 parts (0 on the bottom side), 17 nets.

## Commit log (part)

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2026-04-11 Universalize: si5351.c
2026-04-11 Universalize: mixer.{c,h}, usb_api_register.c
2026-04-11 Universalize: operacake_sctimer.c
2026-04-11 Universalize: rf_path.{c,h}
2026-04-11 Universalize: sgpio.{c,h}
2026-04-11 Universalize: hackrf_ui.c
2026-04-11 Universalize: hackrf_core.{c,h}, selftest.h, tune_config.h
2026-04-11 Add UNIVERSAL firmware build to GitHub Actions.
2026-04-11 Universalize: firmware/hackrf_usb
2026-04-11 firmware: Use macros to simplify platform-specific code.
2026-04-11 max283x: Add macros to simplify variant-specific dispatch.
2026-04-11 Jenkinsfile: add tests with BOARD=UNIVERSAL.
2026-04-11 Add radio configuration update callback
2026-04-11 Add macros to clarify fixed-point constants.
2026-04-13 Use fixed-point type for tuning functions
2026-04-13 Add program option to tuning functions
2026-04-13 Restrict tuning frequency in tuning functions
2026-04-13 Clean up static applied_afe_rate
2026-04-13 Store rotation in 32-bit format
2026-04-14 Remove some superfluous parentheses.
2026-04-14 Ensure correct gains displayed in PortaPack UI
    Previously it was possible, though rare, for an update of an RX gain
    setting to be displayed during TX mode or for an update of a TX gain
    setting to be displayed during RX mode.
2026-04-15 Correct SCU config for CPLD JTAG on Jawbreaker
2026-04-15 Universalize: cpld_jtag.{c,h}
2026-04-15 Universalize: platform_scu.{c,h}
2026-04-15 Universalize: max283x.{c,h}
2026-04-15 Universalize: tuning.{c,h}, tune_config.h
2026-04-16 Add temporary HIL CI fix - sleep 4s after programming the EUT
2026-04-16 Jenkinsfile: ensure usb hub commands are wrapped in retry blocks
2026-04-21 Change Praline CLKIN default to P1_CLKIN
    Previously the CLKIN switch defaulted to P22_CLKIN, enabling usage of
    the clock input on pin header P22 but not on SMA port P1. This change
    enables use of clock input on P1 and disables P22_CLKIN by default.
2026-04-21 Add CLKIN control option to hackrf_clock
2026-04-21 By default, turn off bias tee when radio idle
    This matches the behavior before #1648.
2026-04-21 Fix explicit TX interpolation
2026-04-22 Add new usb_bulk_buffer.
2026-04-22 NAK the request that takes us out of TX mode until buffer flushed.
2026-04-22 For API >= 1.12, get buffer size when opening device.
2026-04-22 Reduce memory transfer size to 8KB.
2026-04-22 Read USB API version in hackrf_open() and cache it.
2026-04-22 Flush both buffers before leaving TX mode.
2026-04-22 Add vendor request to retrieve buffer size.
2026-04-23 firmware: move cpu clock logic to cpu_clock.h|c
2026-04-23 firmware: move clock generator logic to clock_gen.h|c
2026-04-23 firmware: move led logic to leds.h|c
2026-04-23 firmware: move clkin_ctrl_set to clkin.h|c
2026-04-23 firmware: move clock-associated gpio functions to clkin.x and rename to clock_io.h|c
2026-04-24 firmware: rename hackrf_core.x to pins.x
2026-04-24 firmware: move platform preprocessor definitions to cmake
2026-04-24 firmware: alternate solution to 'pragma: keep'
2026-04-24 ci: add resource locks to HIL USB hubs to allow for concurrent builds
2026-04-25 Fix clear pending int to proper bit of MR0
2026-04-27 - Add input PPS synchronization - Add get input PPS active host command
2026-04-30 firmware: move radio_t object instance to hackrf_usb binary
2026-04-30 firmware: move spi_bus_ssp0, spi_bus_ssp1 driver instances to spi_bus.x
2026-04-30 firmware: move w25q80vc driver instance to w25q80bv.x
2026-04-30 firmware: move max283x driver instance to max283x.x
2026-04-30 ui_rad1o: use a helper function for printing frequencies.
2026-04-30 firmware: rename si5351c driver instance 'clock_gen' to 'si5351c'
2026-04-30 firmware: move si5351c driver instance 'clock_gen' to si5351c.x
2026-04-30 firmware: move mixer object's extern instance to mixer.h
2026-04-30 firmware: move rf_path object instance to rf_path.x
2026-04-30 picoprintf: use #pragma once.
2026-04-30 picoprintf: Fix unused variable warnings with GCC 15.2.
2026-04-30 picoprintf: remove unnecessary picobool.h.
    We don't require workarounds for ancient C environments.
2026-04-30 picoprintf: Standardize code style.
2026-04-30 rad1o: Add formatting support to rad1o_lcdPrint.
2026-04-30 ui_rad1o: Eliminate use of sprintf.
2026-04-30 GPIO/SCU: Use the same 'tx_amp' field for both H1 and rad1o.
2026-04-30 Add rad1o and Jawbreaker support to universal builds.
2026-04-30 firmware: move sgpio_config configuration instance to sgpio.x
2026-04-30 firmware: move ice40 driver instance to ice40_spi.x
2026-04-30 firmware: remove drivers.x
2026-05-01 Improve pins_shutdown()
2026-05-03 Add register definitions and accessors for Si5351C.
2026-05-07 Fix IWYU --keep syntax for compatibility with 0.22
2026-05-07 Remove redundant includes
2026-05-11 fix CI build
2026-05-12 revert LZ4 bufs reservations, get back memory
2026-05-13 Move cpld_jtag_sram_load() into cpld_jtag.c.
2026-05-14 si5351c: API: distinguish between PLL IDs and PLL masks.
    We're going to want a type that just identifies one PLL, and is
    consistent with how the PLLs are numbered in register settings.
    The current si5351c_pll_t is a bitmask which allows referring to
    both PLLs. Let's make that a different type, and name things more
    clearly when using it.
2026-05-14 si5351c: internal: Add register definitions and helpers.
2026-05-18 Add script to extract font data to an image file for editing.
2026-05-18 Add 'kHz' characters to 16x14 font.
2026-05-18 Fix up IWYU issues in cpld_jtag.{c,h}.
2026-05-18 Move ssp1_set_mode_max283x call into max283x_setup.
2026-05-18 Move max283x-related bits out of pins_setup.
2026-05-18 Move w25q80bv-related bits out of pins_setup.
2026-05-18 Move mixer-related bits out of pins_setup.
2026-05-18 Move sgpio-related bits out of pins_setup.
2026-05-18 Move max5864-related bits out of pins_setup.
2026-05-18 Move ice40-related bits out of pins_setup.
2026-05-19 si5351c: Wait for SYS_INIT flag to clear during startup.
2026-05-19 si5351c: Make clk array persistent, setup in init, include OE flags.
2026-05-19 Move LPC43xx I2C instances and configs to ipc_lpc.{c,h}.
2026-05-19 Jenkinsfile: ensure device resets occur between test runs
2026-05-20 - Note on R9 boards that are better for sync - Wrap HTime documentation sources to 80 cols
2026-05-21 si5351c: Add control of MCU_CLKIN output.
2026-05-21 fix iwyu errors
2026-05-22 Fix reads with hackrf_spiflash when size is a multiple of 64 bytes.
2026-05-29 host: defensive fixes, TX safety, Pro FPGA tool, and test harness
    Batch 1: Library defensive fixes
    - Fix off-by-one in hackrf_device_list_bus_sharing
    - Guard open_devices decrement in hackrf_close against NULL
    - Add NULL guard to hackrf_device_list_free
    - Fix resource leaks on hackrf_open_setup failure paths
    - Fix TX left on after start_tx failure
2026-05-29 tools: fix spiflash -C option and add debug --cpld-checksum flag
    Fix three issues found during hardware validation:
    1. hackrf_spiflash: -C/--clear option was inconsistent. The long option
    table used 'C' but the optstring and switch case still used 'c',
    making --clear unreachable and conflicting with --compatibility.
    Fixed optstring, switch case, and help text to use 'C' consistently.
    2. hackrf_debug: Added missing --cpld-checksum / -k CLI flag to expose
2026-05-29 ci-scripts: add multi-run stability stats to hackrf_array_cal.py
    Added --runs N option to capture multiple times and compute statistics:
    - Phase offset mean, std dev, min, max, range
    - Magnitude ratio mean and std dev
    - Peak frequency stability
    - Stability assessment: EXCELLENT/GOOD/FAIR/POOR with advice
    Hardware validated: Pro r1.2 + One r9 with shared clock show POOR
2026-05-29 ci-scripts: add hackrf_beamform.py for live 2-element beamforming
    New Python script performs repeated snapshot beamforming with two
    clock-locked HackRFs. Features:
    - Captures IQ buffers from both devices in a loop
    - Applies calibration phase offset
    - Scans steering angles (-180° to +180°)
    - Shows ASCII beam pattern with peak marker
2026-05-29 firmware: improve FPGA bitstream guard and clean up CPLD checksum
    - Check applied radio opmode (RADIO_BANK_APPLIED) instead of pending
    transceiver_request.mode to close race window where streaming is
    still active during shutdown.
    - Remove dead checksum_success branch in usb_api_cpld.c; the SRAM-read
    checksum function always returns true.
2026-05-29 docs: add comprehensive achievement report and Mayhem unlock analysis
    ACHIEVEMENTS_REPORT.md: 510-line technical report covering firmware,
    host library, tools, hardware validation, upstream readiness, and
    Mayhem integration points.
    MAYHEM_UNLOCK_ANALYSIS.md: Concrete roadmap for bringing CPLD
    diagnostics, FPGA bitstream switching, and phased-array features to
    the PortaPack Mayhem platform. Includes submodule bump commands and
2026-05-29 docs: add upstream PR prep and sync-start design
    UPSTREAM_PR_PREP.md: Commit breakdown, recommended PR split,
    pre-submission checklist, and draft PR description for
    greatscottgadgets/hackrf.
    SYNC_START_DESIGN.md: Three design options for synchronized
    multi-device RX/TX start — software sync, hardware trigger,
    and USB broadcast — with firmware/host API sketches and
2026-05-29 style: apply clang-format to changed lines in new and modified files
2026-05-29 Add hardware validation scripts for sync-start and FPGA guard
    - test_sync_start.py: validates hackrf_sync_start() on physical devices
    - test_fpga_bitstream_guard.py: validates FPGA bitstream guard rejects
    switches while in RX/TX mode (Pro only)
2026-05-29 Add end-to-end validation report
    Documents hardware test results for Pro and recovery status for One.
2026-05-29 Address reviewer feedback: fix self-test, sync-start, spiflash guard, coherence
    - Accept RFFC5072 ID 4544 (newer chip variant) in self-test
    - Bump USB API version to 0x0113 for sync-start
    - Fix sync-start firmware: skip trigger when mode=OFF
    - Fix sync-start host: add NULL check, mode validation, API guard
    - Add multi-device guard to hackrf_spiflash for write ops
    - Add coherence validation test (clock + trigger arm)
2026-05-29 Add sub-MHz investigation, new capabilities doc, phased array demo
    Sub-1 MHz findings:
    - HackRF Pro can capture down to 200 kHz sample rate using -F flag
    - FPGA handles automatic decimation up to 32x
    - Verified: 500 kHz capture at 500 kHz center, 200 kHz at 100 kHz
    - AM broadcast demodulated successfully at 1 MHz
    New capabilities documented:
2026-05-29 firmware/host: add sync-start vendor request and hackrf_sync_start() API
2026-05-29 host: rewrite coherence test with trigger support and callback machinery
2026-05-29 Refactor libopencm3 build process to avoid races and manage dependencies
2026-06-03 Add SigDigger support information to documentation
2026-06-03 add gateware documentation
2026-06-04 Make switching SPI bus modes automatic.
2026-06-08 si5351c: Move the clk array into the driver struct.
2026-06-08 Remove some superfluous spi_bus_setup calls.
2026-06-10 Update README.md with minimal ethics#1
    What about the application of the Solomonoff induction
    to the RF sensing of human brain?
    https://en.wikipedia.org/wiki/Talk:Solomonoff%27s_theory_of_inductive_inference
    1. If we assume that the algorithmic complexity
    of neural processes is relatively small
    (you could take a look at the Potapov monography
2026-06-12 Fix management of CLKOUT/MCU_CLK synth sharing on H1R9.
2026-06-12 Add portapack_audio_reset_state().
2026-06-12 Add portapack_lcd_sleep_in().
2026-06-12 Add portapack_lcd_display_off().
2026-06-12 portapack: Expose more internal functions.
2026-06-15 Specify I2C clock in kHz, and adjust for CPU clock changes.
2026-06-15 CI: Bump actions/checkout to v6.
2026-06-15 CI: Simplify install steps.
2026-06-15 CI: Build with more CMake and Visual Studio versions.
2026-06-16 fix: add buffer-length check in hackrf_transfer.c
    The hackrf_transfer tool performs memcpy operations into a heap-allocated stream_buf at an offset of stream_tail
2026-06-24 si5351c: Add support for compensating clock reference error.
2026-06-29 radio: add radio_set_config_mode()
2026-06-30 Add multiply & divide implementations for 128-bit unsigned integers.
